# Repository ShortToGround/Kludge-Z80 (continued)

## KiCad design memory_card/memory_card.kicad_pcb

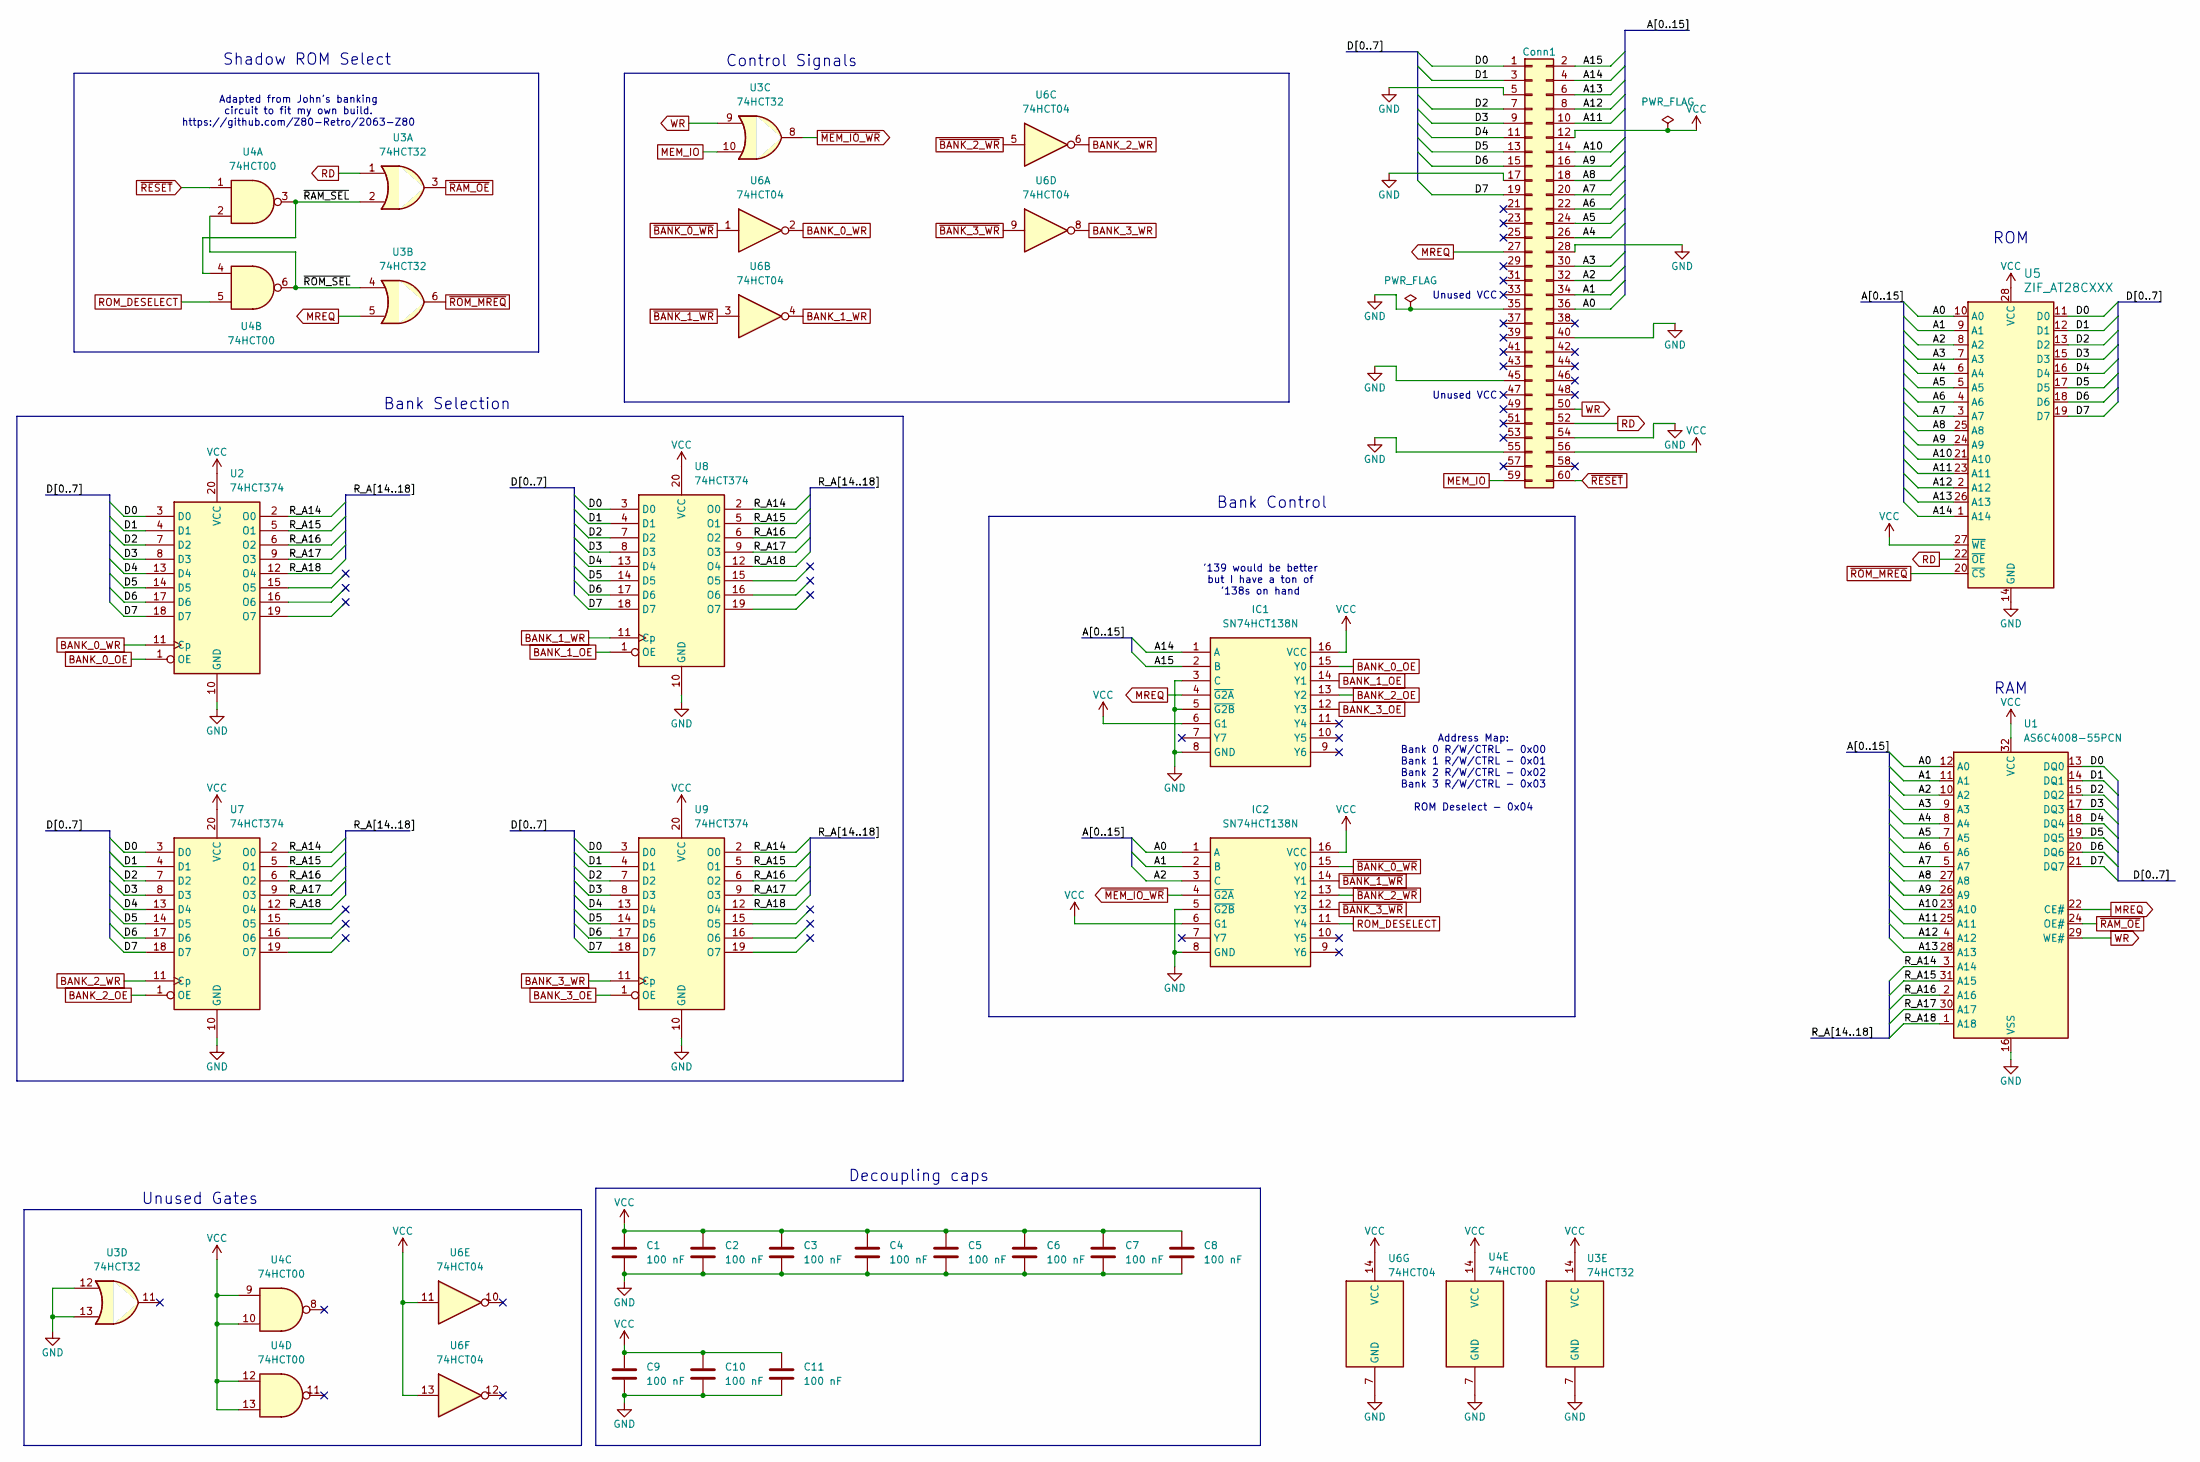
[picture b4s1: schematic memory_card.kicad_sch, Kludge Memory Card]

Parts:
C1, C2, C3, C4, C5, C6, C7, C8, C9, C10, C11: 100 nF; C_Disc_D3.0mm_W1.6mm_P2.50mm
IC1, IC2: SN74HCT138N; DIP-16_W7.62mm_Socket; Mouser Part Number 595-SN74HCT138N
J1: Conn1; PinHeader_2x30_P2.54mm_Vertical
U1: AS6C4008-55PCN; DIP-32_W15.24mm
U2, U7, U8, U9: 74HCT374; DIP-20_W7.62mm_Socket
U3: 74HCT32; DIP-14_W7.62mm_Socket
U4: 74HCT00; DIP-14_W7.62mm_Socket
U5: ZIF_AT28CXXX; DIP_Socket-28_W11.9_W12.7_W15.24_W17.78_W18.5_3M_228-1277-0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
U6: 74HCT04; DIP-14_W7.62mm_Socket

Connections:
/A0: IC2.1 (A), J1.36, U1.12 (A0), U5.10 (A0)
/A1: IC2.2 (B), J1.34, U1.11 (A1), U5.9 (A1)
/A2: IC2.3 (C), J1.32, U1.10 (A2), U5.8 (A2)
/A3: J1.30, U1.9 (A3), U5.7 (A3)
/A4: J1.26, U1.8 (A4), U5.6 (A4)
/A5: J1.24, U1.7 (A5), U5.5 (A5)
/A6: J1.22, U1.6 (A6), U5.4 (A6)
/A7: J1.20, U1.5 (A7), U5.3 (A7)
/A8: J1.18, U1.27 (A8), U5.25 (A8)
/A9: J1.16, U1.26 (A9), U5.24 (A9)
/A10: J1.14, U1.23 (A10), U5.21 (A10)
/A11: J1.10, U1.25 (A11), U5.23 (A11)
/A12: J1.8, U1.4 (A12), U5.2 (A12)
/A13: J1.6, U1.28 (A13), U5.26 (A13)
/A14: IC1.1 (A), J1.4, U5.1 (A14)
/A15: IC1.2 (B), J1.2
/D0: J1.1, U1.13 (DQ0), U2.3 (D0), U5.11 (D0), U7.3 (D0), U8.3 (D0), U9.3 (D0)
/D1: J1.3, U1.14 (DQ1), U2.4 (D1), U5.12 (D1), U7.4 (D1), U8.4 (D1), U9.4 (D1)
/D2: J1.7, U1.15 (DQ2), U2.7 (D2), U5.13 (D2), U7.7 (D2), U8.7 (D2), U9.7 (D2)
/D3: J1.9, U1.17 (DQ3), U2.8 (D3), U5.15 (D3), U7.8 (D3), U8.8 (D3), U9.8 (D3)
/D4: J1.11, U1.18 (DQ4), U2.13 (D4), U5.16 (D4), U7.13 (D4), U8.13 (D4), U9.13 (D4)
/D5: J1.13, U1.19 (DQ5), U2.14 (D5), U5.17 (D5), U7.14 (D5), U8.14 (D5), U9.14 (D5)
/D6: J1.15, U1.20 (DQ6), U2.17 (D6), U5.18 (D6), U7.17 (D6), U8.17 (D6), U9.17 (D6)
/D7: J1.19, U1.21 (DQ7), U2.18 (D7), U5.19 (D7), U7.18 (D7), U8.18 (D7), U9.18 (D7)
/R_A14: U1.3 (A14), U2.2 (O0), U7.2 (O0), U8.2 (O0), U9.2 (O0)
/R_A15: U1.31 (A15), U2.5 (O1), U7.5 (O1), U8.5 (O1), U9.5 (O1)
/R_A16: U1.2 (A16), U2.6 (O2), U7.6 (O2), U8.6 (O2), U9.6 (O2)
/R_A17: U1.30 (A17), U2.9 (O3), U7.9 (O3), U8.9 (O3), U9.9 (O3)
/R_A18: U1.1 (A18), U2.12 (O4), U7.12 (O4), U8.12 (O4), U9.12 (O4)
/~RAM_SEL: U3.2, U4.3, U4.4
/~ROM_SEL: U3.4, U4.2, U4.6
BANK_0_OE: IC1.15 (Y0), U2.1 (OE)
BANK_0_WR: U2.11 (Cp), U6.2
BANK_1_OE: IC1.14 (Y1), U8.1 (OE)
BANK_1_WR: U6.4, U8.11 (Cp)
BANK_2_OE: IC1.13 (Y2), U7.1 (OE)
BANK_2_WR: U6.6, U7.11 (Cp)
BANK_3_OE: IC1.12 (Y3), U9.1 (OE)
BANK_3_WR: U6.8, U9.11 (Cp)
GND: C1.2, C2.2, C3.2, C4.2, C5.2, C6.2, C7.2, C8.2, C9.2, C10.2, C11.2, IC1.3 (C), IC1.5 (~G2B), IC1.8 (GND), IC2.5 (~G2B), IC2.8 (GND), J1.5, J1.17, J1.28, J1.35, J1.40, J1.45, J1.54, J1.55, U1.16 (VSS), U2.10 (GND), U3.7 (GND), U3.12, U3.13, U4.7 (GND), U5.14 (GND), U6.7 (GND), U7.10 (GND), U8.10 (GND), U9.10 (GND)
MEM_IO: J1.59, U3.10
MREQ: IC1.4 (~G2A), J1.27, U1.22 (CE#), U3.5
RD: J1.52, U3.1, U5.22 (~OE)
ROM_DESELECT: IC2.11 (Y4), U4.5
VCC: C1.1, C2.1, C3.1, C4.1, C5.1, C6.1, C7.1, C8.1, C9.1, C10.1, C11.1, IC1.6 (G1), IC1.16 (VCC), IC2.6 (G1), IC2.16 (VCC), J1.12, J1.56, U1.32 (VCC), U2.20 (VCC), U3.14 (VCC), U4.9, U4.10, U4.12, U4.13, U4.14 (VCC), U5.27 (~WE), U5.28 (VCC), U6.11, U6.13, U6.14 (VCC), U7.20 (VCC), U8.20 (VCC), U9.20 (VCC)
WR: J1.50, U1.29 (WE#), U3.9
~BANK_0_WR: IC2.15 (Y0), U6.1
~BANK_1_WR: IC2.14 (Y1), U6.3
~BANK_2_WR: IC2.13 (Y2), U6.5
~BANK_3_WR: IC2.12 (Y3), U6.9
~MEM_IO_WR: IC2.4 (~G2A), U3.8
~RAM_OE: U1.24 (OE#), U3.3
~RESET: J1.60, U4.1
~ROM_MREQ: U3.6, U5.20 (~CS)

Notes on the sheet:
Unused VCC
Control Signals
Unused Gates
ROM
Address Map: Bank 0 R/W/CTRL - 0x00 Bank 1 R/W/CTRL - 0x01 Bank 2 R/W/CTRL - 0x02 Bank 3 R/W/CTRL - 0x03 ROM Deselect - 0x04
Adapted from John's banking circuit to fit my own build. https://github.com/Z80-Retro/2063-Z80
Shadow ROM Select
Decoupling caps
Bank Control
RAM
Bank Selection
'139 would be better but I have a ton of '138s on hand

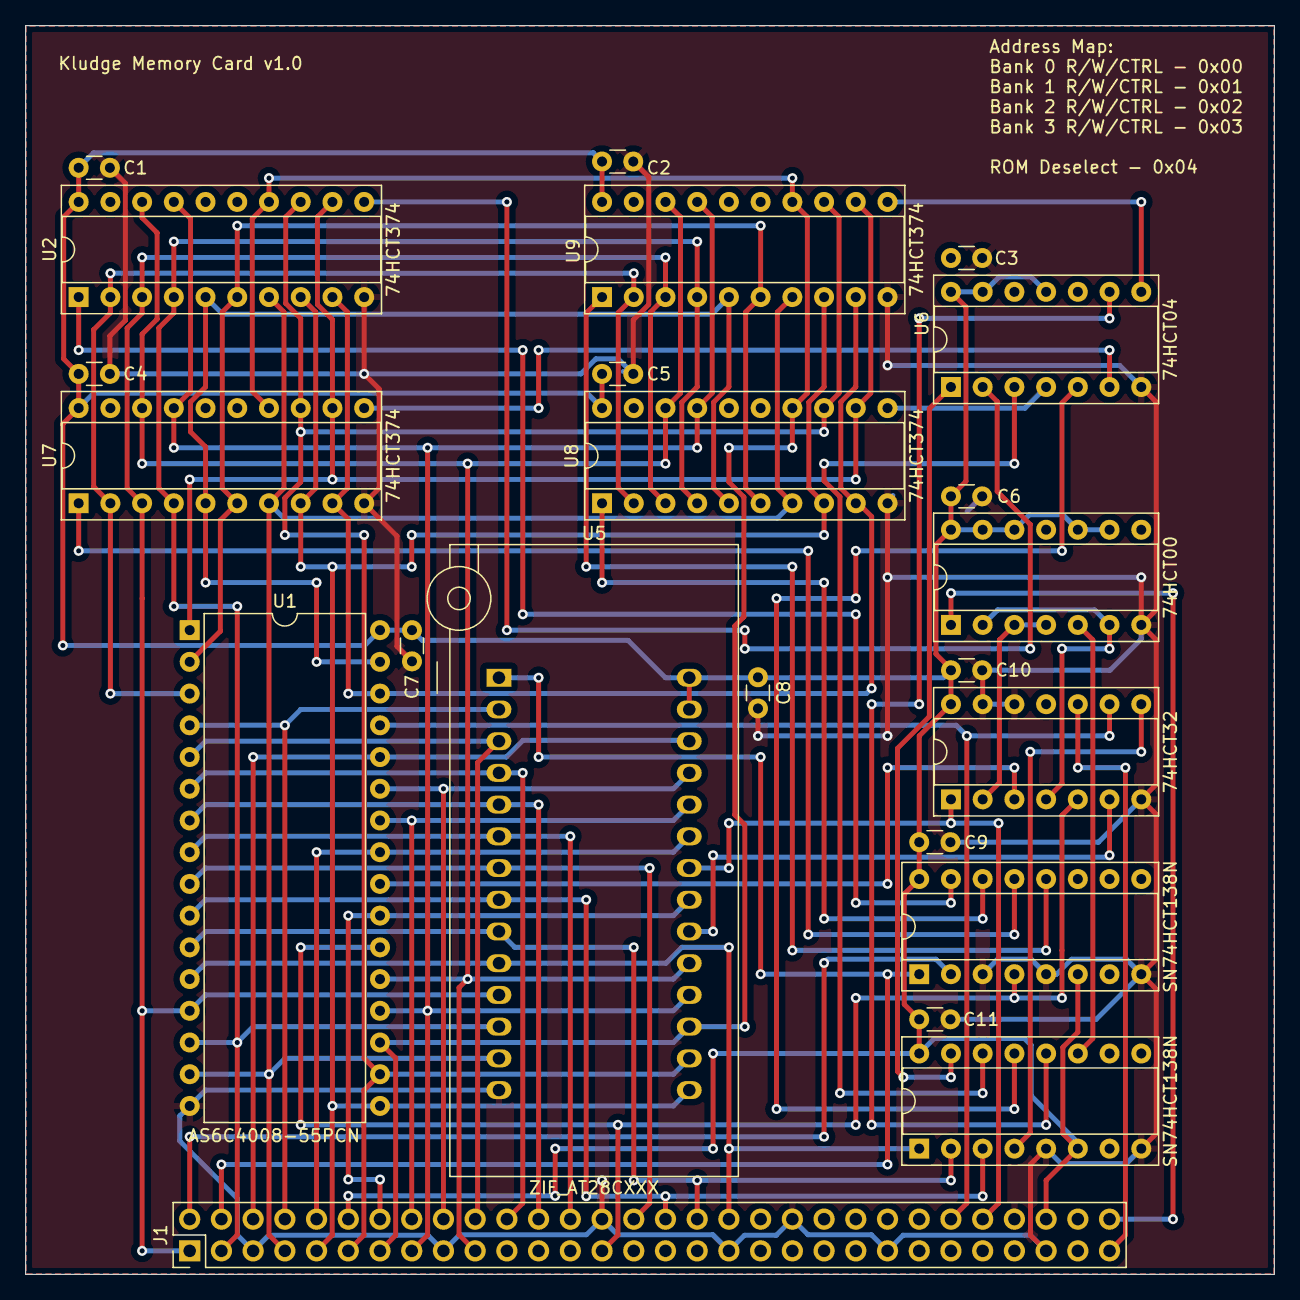
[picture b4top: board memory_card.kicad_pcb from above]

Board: 2 copper layers, 100.0 x 100.0 mm, 23 parts (0 on the bottom side), 54 nets.

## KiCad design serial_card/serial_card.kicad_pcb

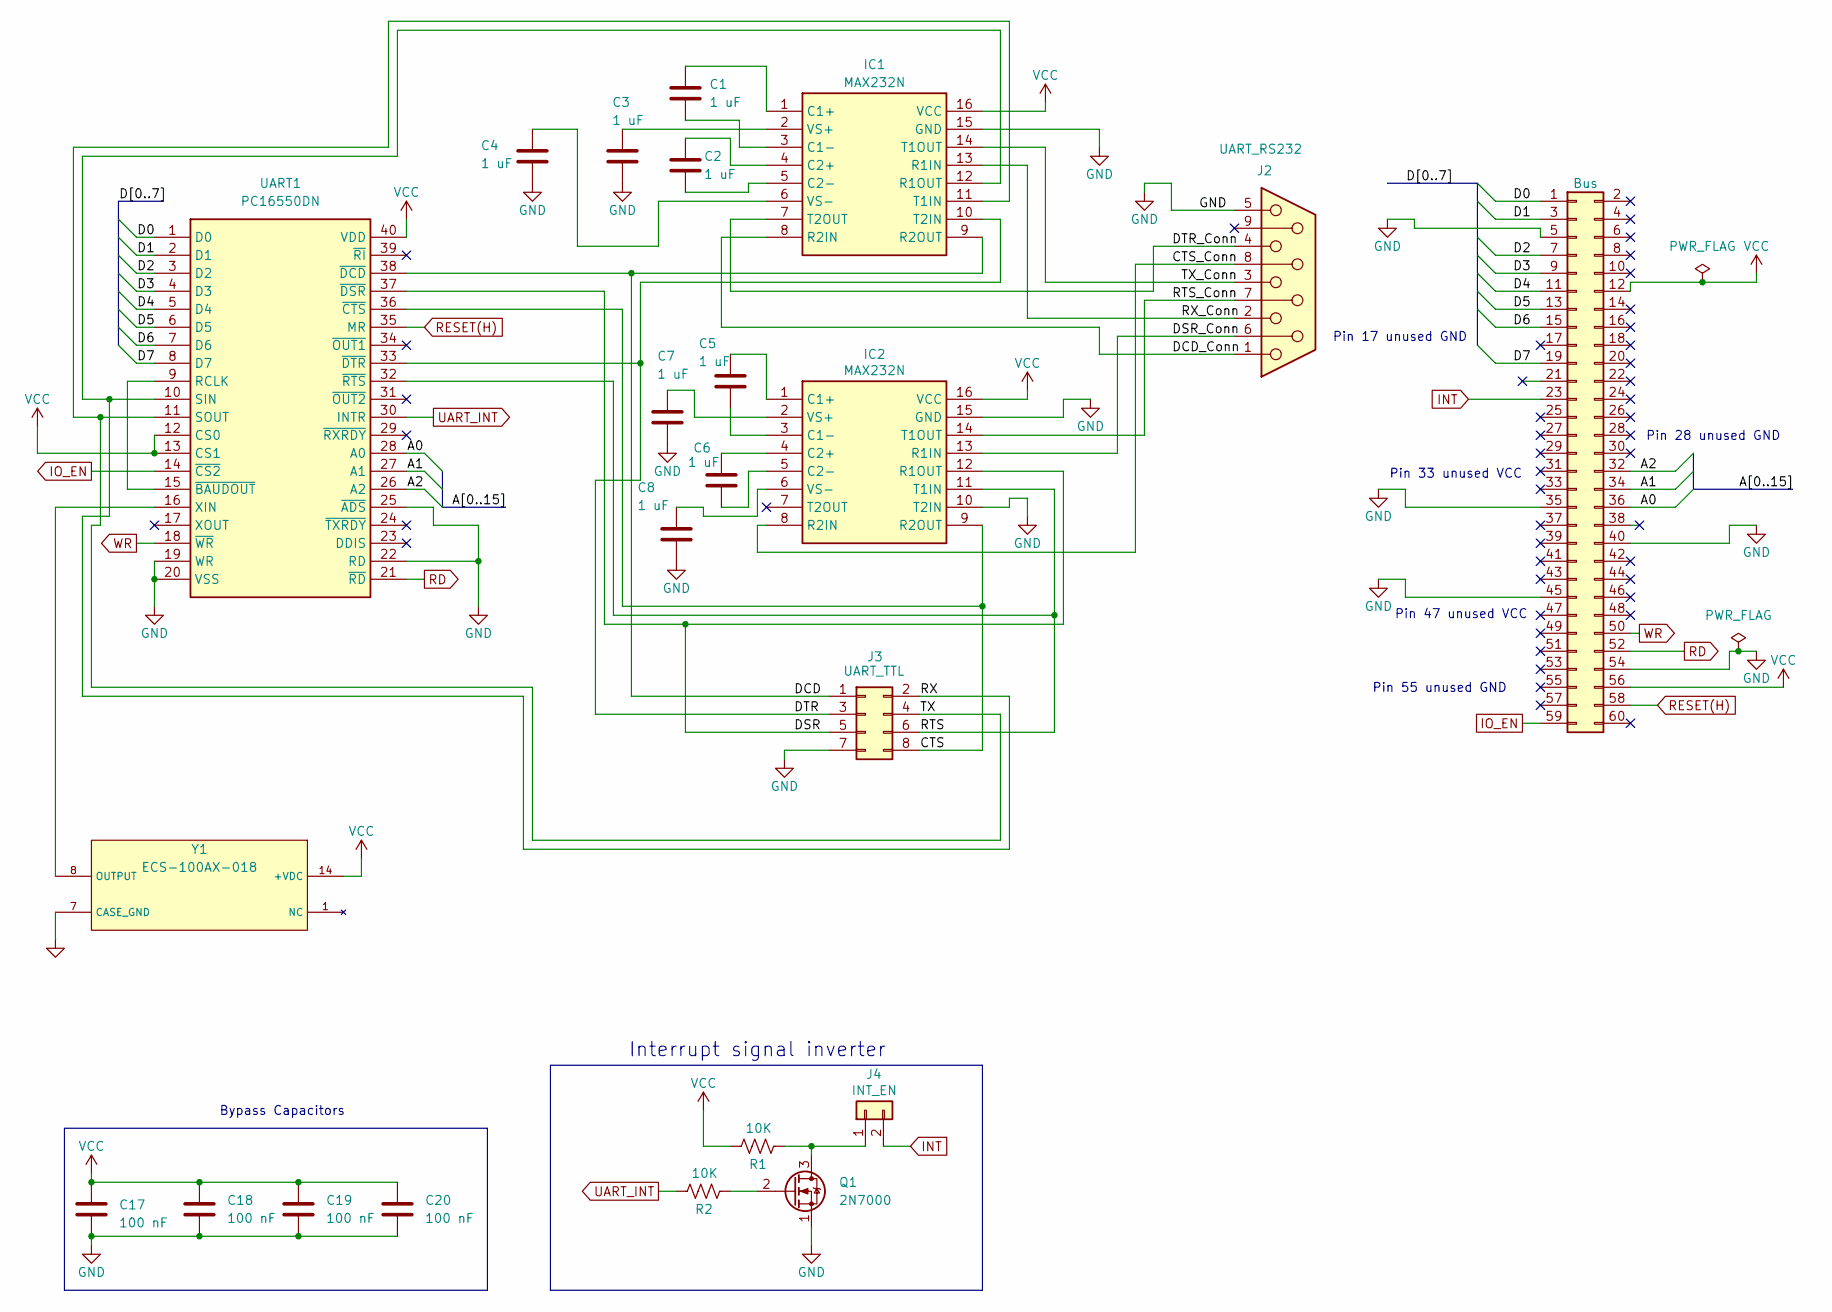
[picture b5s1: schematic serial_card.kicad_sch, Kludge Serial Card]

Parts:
C1, C2, C3, C4, C5, C6, C7, C8: 1 uF; C_Disc_D3.0mm_W1.6mm_P2.50mm
C17, C18, C19, C20: 100 nF; C_Disc_D3.0mm_W1.6mm_P2.50mm
IC1, IC2: MAX232N; DIP-16_W7.62mm; Mouser Part Number 595-MAX232N
J1: Bus; PinHeader_2x30_P2.54mm_Vertical
J2: UART_RS232; CONN_A-DS 09 A&slash_KG-T4S_ASM
J3: UART_TTL; PinHeader_2x04_P2.54mm_Vertical
J4: INT_EN; PinHeader_1x02_P2.54mm_Vertical
Q1: 2N7000; TO-92_Inline
R1, R2: 10K; R_Axial_DIN0207_L6.3mm_D2.5mm_P10.16mm_Horizontal
UART1: PC16550DN; DIP-40_W15.24mm_Socket; Mouser Part Number 926-PC16550DN/NOPB
Y1: ECS-100AX-018; OSC_ECS-100AX-018; DigiKey_Part_Number X939-ND

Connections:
/A0: J1.36, UART1.28 (A0)
/A1: J1.34, UART1.27 (A1)
/A2: J1.32, UART1.26 (A2)
/CTS: IC2.9 (R2OUT), J3.8, UART1.36 (~CTS)
/CTS_Conn: IC2.8 (R2IN), J2.8
/D0: J1.1, UART1.1 (D0)
/D1: J1.3, UART1.2 (D1)
/D2: J1.7, UART1.3 (D2)
/D3: J1.9, UART1.4 (D3)
/D4: J1.11, UART1.5 (D4)
/D5: J1.13, UART1.6 (D5)
/D6: J1.15, UART1.7 (D6)
/D7: J1.19, UART1.8 (D7)
/DCD: IC1.9 (R2OUT), J3.1, UART1.38 (~DCD)
/DCD_Conn: IC1.8 (R2IN), J2.1
/DSR: IC2.12 (R1OUT), J3.5, UART1.37 (~DSR)
/DSR_Conn: IC2.13 (R1IN), J2.6
/DTR: IC1.10 (T2IN), J3.3, UART1.33 (~DTR)
/DTR_Conn: IC1.7 (T2OUT), J2.4
/RTS: IC2.11 (T1IN), J3.6, UART1.32 (~RTS)
/RTS_Conn: IC2.14 (T1OUT), J2.7
/RX: IC1.12 (R1OUT), J3.2, UART1.10 (SIN)
/RX_Conn: IC1.13 (R1IN), J2.2
/TX: IC1.11 (T1IN), J3.4, UART1.11 (SOUT)
/TX_Conn: IC1.14 (T1OUT), J2.3
GND: C3.2, C4.2, C7.2, C8.2, C17.2, C18.2, C19.2, C20.2, IC1.15 (GND), IC2.10 (T2IN), IC2.15 (GND), J1.5, J1.35, J1.40, J1.45, J1.54, J2.5, J3.7, Q1.1 (S), UART1.19 (WR), UART1.20 (VSS), UART1.22 (RD), UART1.25 (~ADS), Y1.7 (CASE_GND)
INT: J1.23, J4.2
IO_EN: J1.59, UART1.14 (~CS2)
unnamed: C1.1, IC1.1 (C1+)
unnamed: C1.2, IC1.3 (C1-)
unnamed: C2.1, IC1.4 (C2+)
unnamed: C2.2, IC1.5 (C2-)
unnamed: C3.1, IC1.2 (VS+)
unnamed: C4.1, IC1.6 (VS-)
unnamed: C5.1, IC2.1 (C1+)
unnamed: C5.2, IC2.3 (C1-)
unnamed: C6.1, IC2.4 (C2+)
unnamed: C6.2, IC2.5 (C2-)
unnamed: C7.1, IC2.2 (VS+)
unnamed: C8.1, IC2.6 (VS-)
unnamed: J4.1, Q1.3 (D), R1.1
unnamed: Q1.2 (G), R2.1
unnamed: UART1.9 (RCLK), UART1.15 (~BAUDOUT)
unnamed: UART1.16 (XIN), Y1.8 (OUTPUT)
RD: J1.52, UART1.21 (~RD)
RESET(H): J1.58, UART1.35 (MR)
UART_INT: R2.2, UART1.30 (INTR)
VCC: C17.1, C18.1, C19.1, C20.1, IC1.16 (VCC), IC2.16 (VCC), J1.12, J1.56, R1.2, UART1.12 (CS0), UART1.13 (CS1), UART1.40 (VDD), Y1.14 (+VDC)
WR: J1.50, UART1.18 (~WR)

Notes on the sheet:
Pin 47 unused VCC
Pin 28 unused GND
Pin 33 unused VCC
Interrupt signal inverter
Pin 55 unused GND
Bypass Capacitors
Pin 17 unused GND

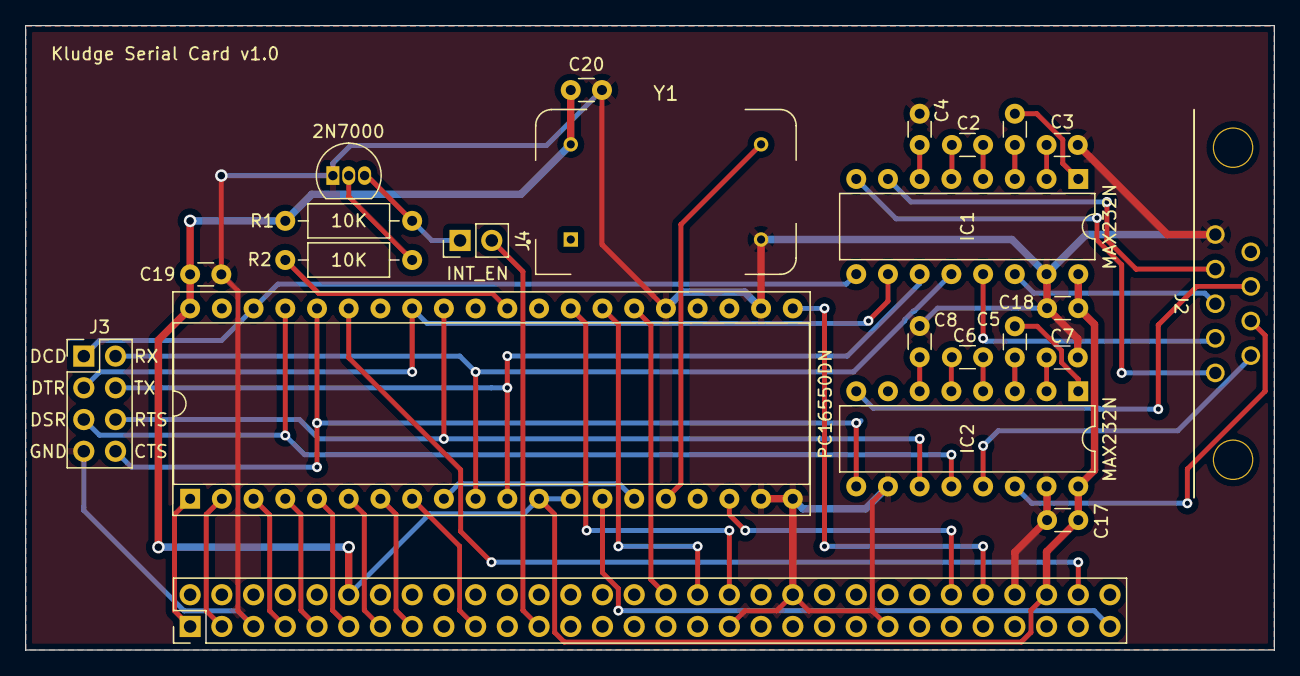
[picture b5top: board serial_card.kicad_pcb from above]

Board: 2 copper layers, 100.0 x 50.0 mm, 23 parts (0 on the bottom side), 49 nets.

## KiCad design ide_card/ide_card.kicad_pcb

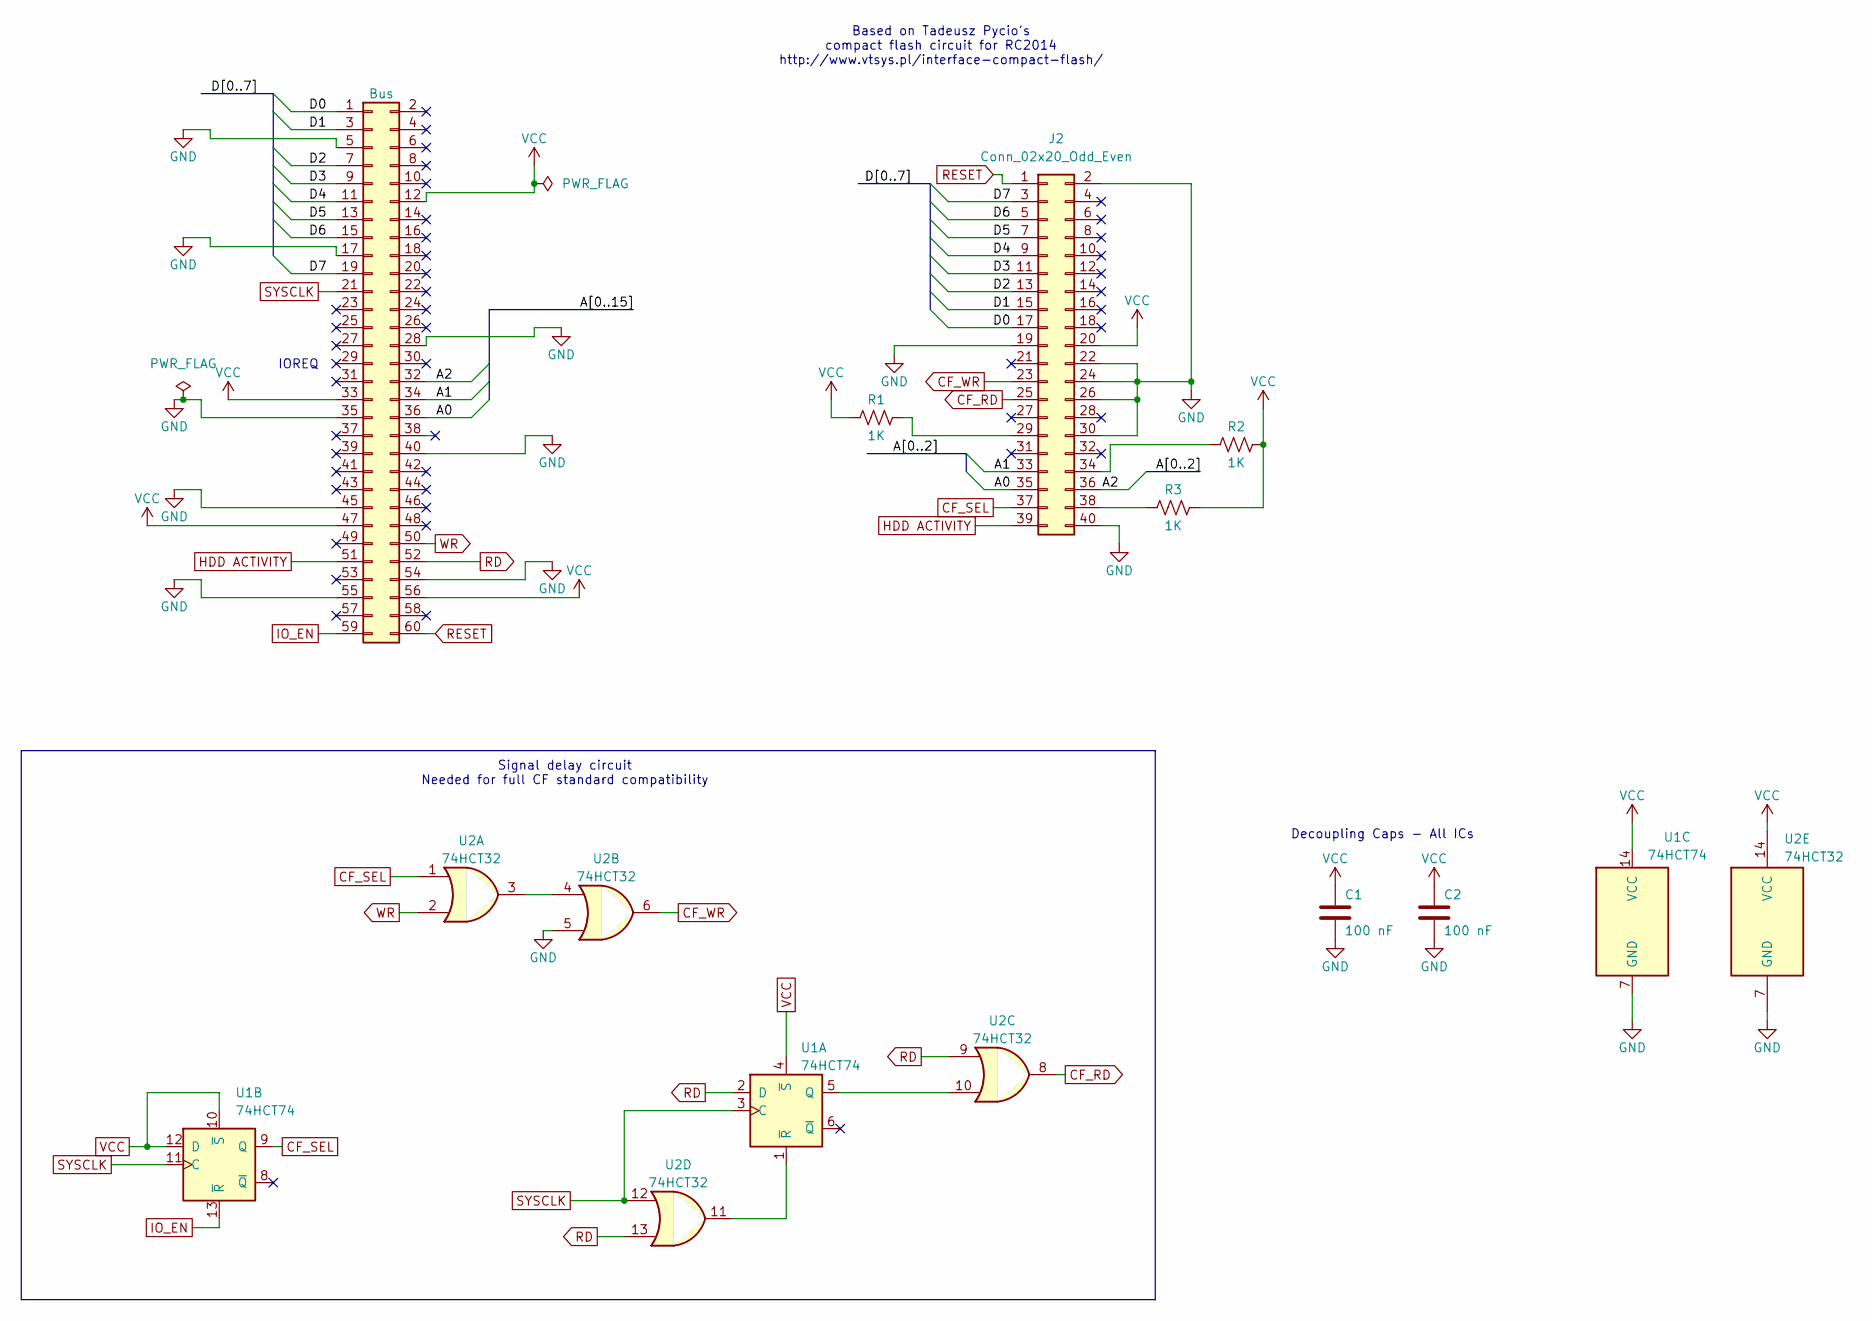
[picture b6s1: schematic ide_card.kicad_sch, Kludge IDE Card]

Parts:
C1, C2: 100 nF; C_Disc_D3.0mm_W1.6mm_P2.54mm
J1: Bus; PinHeader_2x30_P2.54mm_Vertical
J2: Conn_02x20_Odd_Even; IDC-Header_2x20_P2.54mm_Horizontal
R1, R2, R3: 1K; R_Axial_DIN0207_L6.3mm_D2.5mm_P10.16mm_Horizontal
U1: 74HCT74; DIP-14_W7.62mm
U2: 74HCT32; DIP-14_W7.62mm

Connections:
/A0: J1.36, J2.35
/A1: J1.34, J2.33
/A2: J1.32, J2.36
/D0: J1.1, J2.17
/D1: J1.3, J2.15
/D2: J1.7, J2.13
/D3: J1.9, J2.11
/D4: J1.11, J2.9
/D5: J1.13, J2.7
/D6: J1.15, J2.5
/D7: J1.19, J2.3
CF_RD: J2.25, U2.8
CF_SEL: J2.37, U1.9 (Q), U2.1
CF_WR: J2.23, U2.6
GND: C1.2, C2.2, J1.5, J1.17, J1.28, J1.35, J1.40, J1.45, J1.54, J1.55, J2.2, J2.19, J2.22, J2.24, J2.26, J2.30, J2.40, U1.7 (GND), U2.5, U2.7 (GND)
HDD ACTIVITY: J1.51, J2.39
IO_EN: J1.59, U1.13 (~R)
unnamed: J2.29, R1.2
unnamed: J2.34, R2.1
unnamed: J2.38, R3.1
unnamed: U1.5 (Q), U2.10
unnamed: U1.1 (~R), U2.11
unnamed: U2.3, U2.4
RD: J1.52, U1.2 (D), U2.9, U2.13
RESET: J1.60, J2.1
SYSCLK: J1.21, U1.3 (C), U1.11 (C), U2.12
VCC: C1.1, C2.1, J1.12, J1.33, J1.47, J1.56, J2.20, R1.1, R2.2, R3.2, U1.4 (~S), U1.10 (~S), U1.12 (D), U1.14 (VCC), U2.14 (VCC)
WR: J1.50, U2.2

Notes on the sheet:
IOREQ
Signal delay circuit Needed for full CF standard compatibility
Decoupling Caps - All ICs
Based on Tadeusz Pycio's compact flash circuit for RC2014 http://www.vtsys.pl/interface-compact-flash/

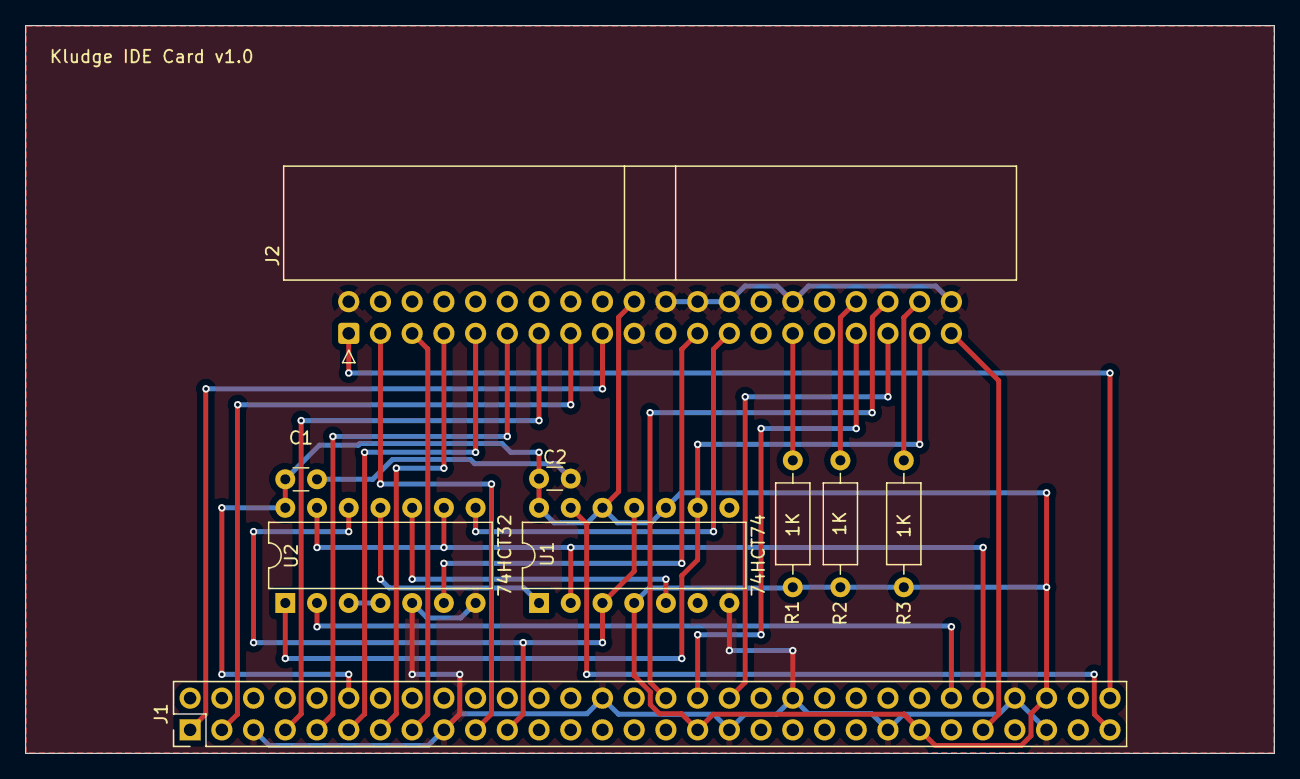
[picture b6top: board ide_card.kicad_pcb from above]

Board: 2 copper layers, 100.0 x 58.3 mm, 9 parts (0 on the bottom side), 28 nets.

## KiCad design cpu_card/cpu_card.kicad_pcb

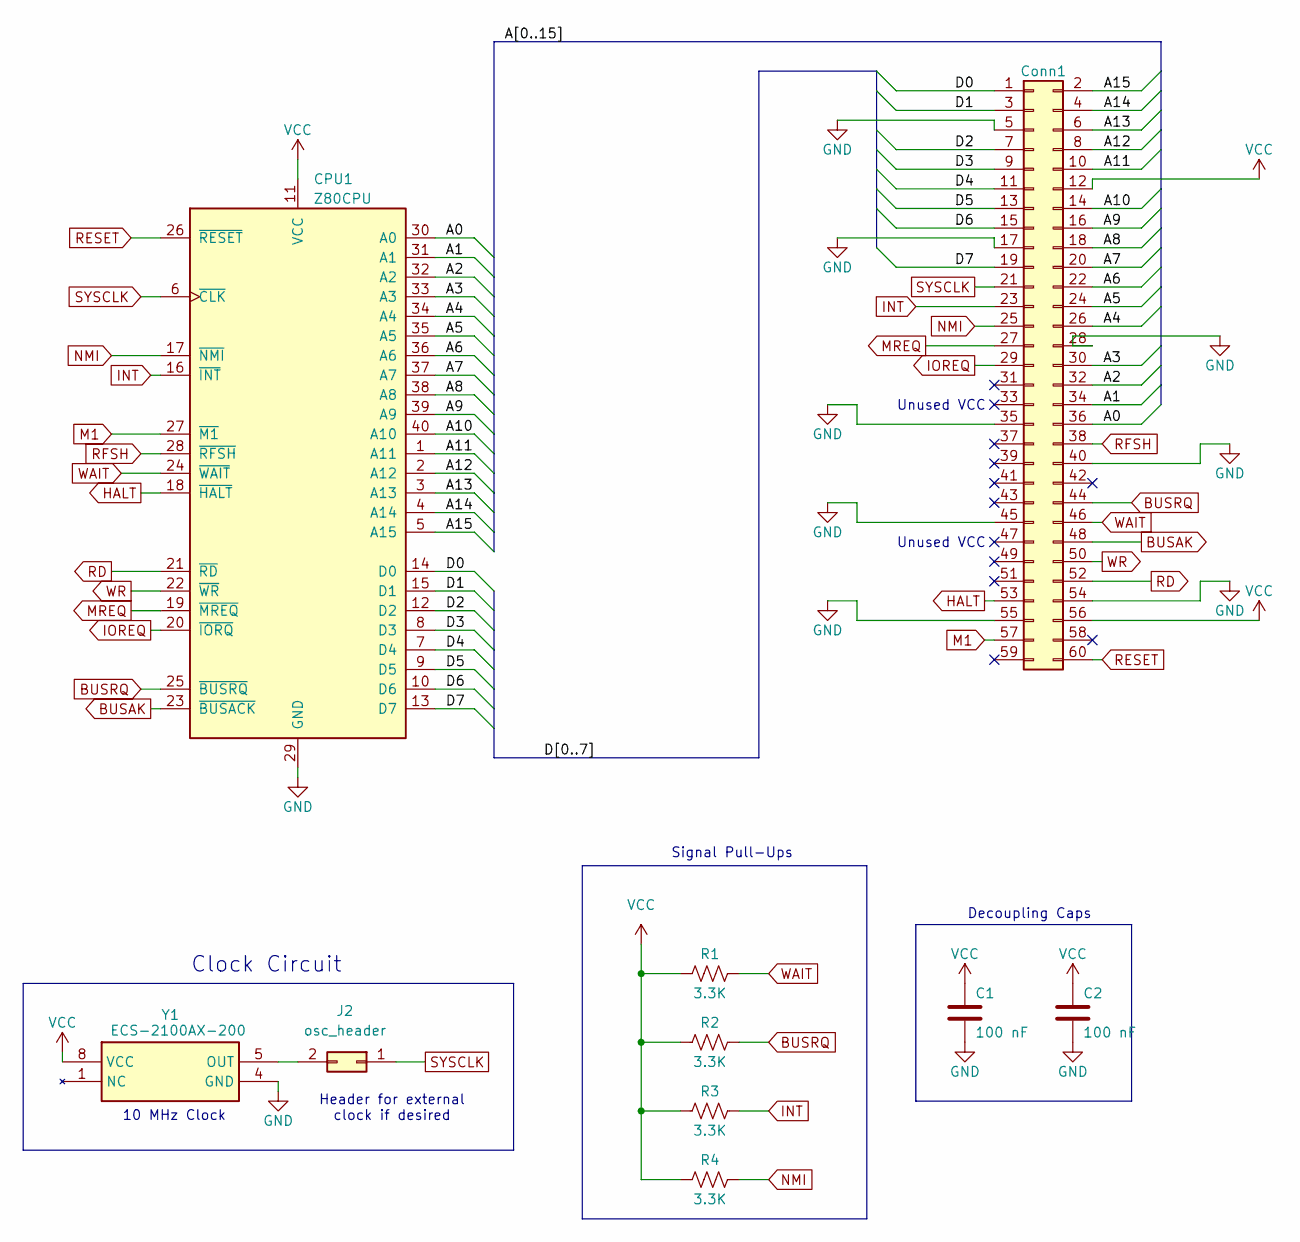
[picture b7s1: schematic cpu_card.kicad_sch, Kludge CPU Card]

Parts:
C1, C2: 100 nF; C_Disc_D3.0mm_W1.6mm_P2.54mm
CPU1: Z80CPU; DIP-40_W15.24mm_Socket
J1: Conn1; PinHeader_2x30_P2.54mm_Vertical
J2: osc_header; PinHeader_2x01_P2.54mm_Vertical
R1, R2, R3, R4: 3.3K; R_Axial_DIN0207_L6.3mm_D2.5mm_P10.16mm_Horizontal
Y1: ECS-2100AX-200; ECS-2100AX-100; Manufacturer_Part_Number ECS-2100AX-100

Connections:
/A0: CPU1.30 (A0), J1.36
/A1: CPU1.31 (A1), J1.34
/A2: CPU1.32 (A2), J1.32
/A3: CPU1.33 (A3), J1.30
/A4: CPU1.34 (A4), J1.26
/A5: CPU1.35 (A5), J1.24
/A6: CPU1.36 (A6), J1.22
/A7: CPU1.37 (A7), J1.20
/A8: CPU1.38 (A8), J1.18
/A9: CPU1.39 (A9), J1.16
/A10: CPU1.40 (A10), J1.14
/A11: CPU1.1 (A11), J1.10
/A12: CPU1.2 (A12), J1.8
/A13: CPU1.3 (A13), J1.6
/A14: CPU1.4 (A14), J1.4
/A15: CPU1.5 (A15), J1.2
/D0: CPU1.14 (D0), J1.1
/D1: CPU1.15 (D1), J1.3
/D2: CPU1.12 (D2), J1.7
/D3: CPU1.8 (D3), J1.9
/D4: CPU1.7 (D4), J1.11
/D5: CPU1.9 (D5), J1.13
/D6: CPU1.10 (D6), J1.15
/D7: CPU1.13 (D7), J1.19
BUSAK: CPU1.23 (~BUSACK), J1.48
BUSRQ: CPU1.25 (~BUSRQ), J1.44, R2.1
GND: C1.2, C2.2, CPU1.29 (GND), J1.5, J1.17, J1.28, J1.35, J1.40, J1.45, J1.54, J1.55, Y1.4 (GND)
HALT: CPU1.18 (~HALT), J1.53
INT: CPU1.16 (~INT), J1.23, R3.1
IOREQ: CPU1.20 (~IORQ), J1.29
M1: CPU1.27 (~M1), J1.57
MREQ: CPU1.19 (~MREQ), J1.27
NMI: CPU1.17 (~NMI), J1.25, R4.1
unnamed: J2.2, Y1.5 (OUT)
RD: CPU1.21 (~RD), J1.52
RESET: CPU1.26 (~RESET), J1.60
RFSH: CPU1.28 (~RFSH), J1.38
SYSCLK: CPU1.6 (~CLK), J1.21, J2.1
VCC: C1.1, C2.1, CPU1.11 (VCC), J1.12, J1.56, R1.2, R2.2, R3.2, R4.2, Y1.8 (VCC)
WAIT: CPU1.24 (~WAIT), J1.46, R1.1
WR: CPU1.22 (~WR), J1.50

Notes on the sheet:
10 MHz Clock
Clock Circuit
Unused VCC
Signal Pull-Ups
Header for external clock if desired
Decoupling Caps

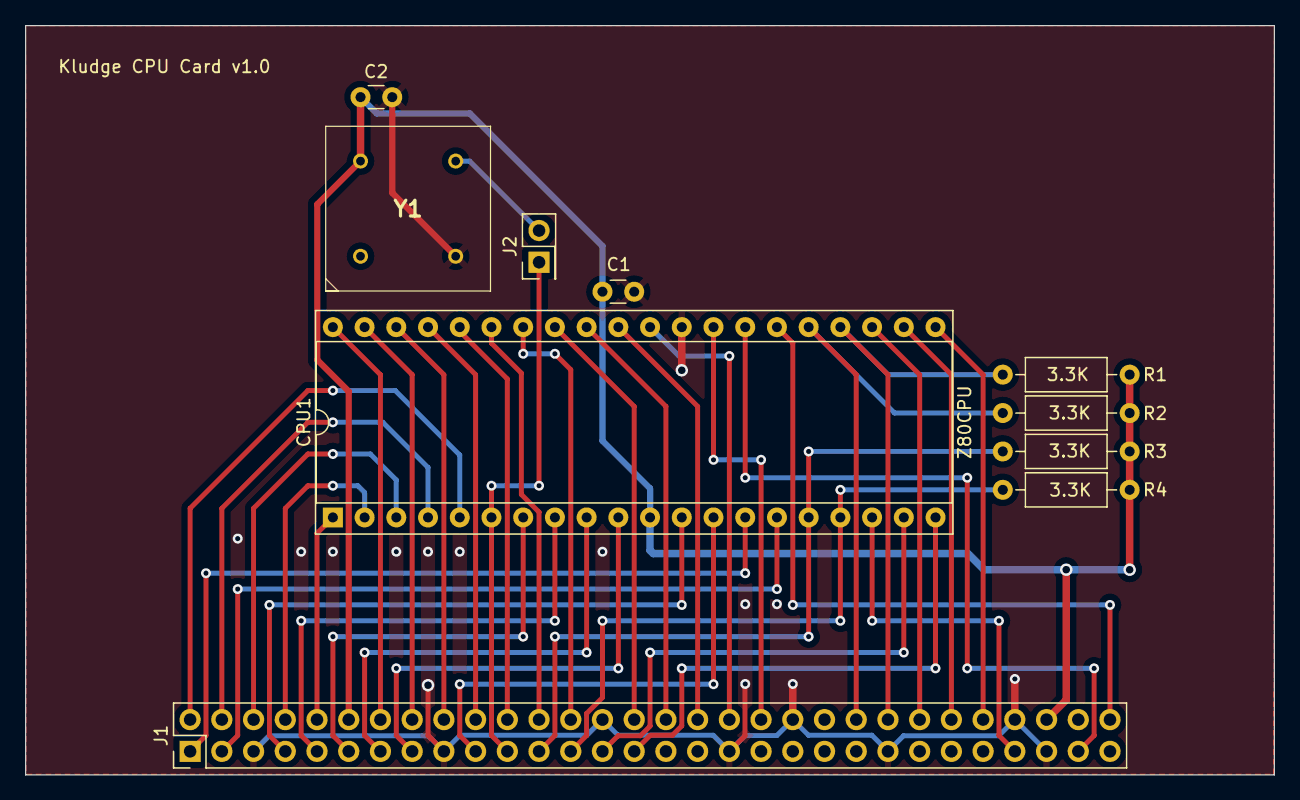
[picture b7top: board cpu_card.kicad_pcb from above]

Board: 2 copper layers, 100.0 x 60.0 mm, 10 parts (0 on the bottom side), 41 nets.
